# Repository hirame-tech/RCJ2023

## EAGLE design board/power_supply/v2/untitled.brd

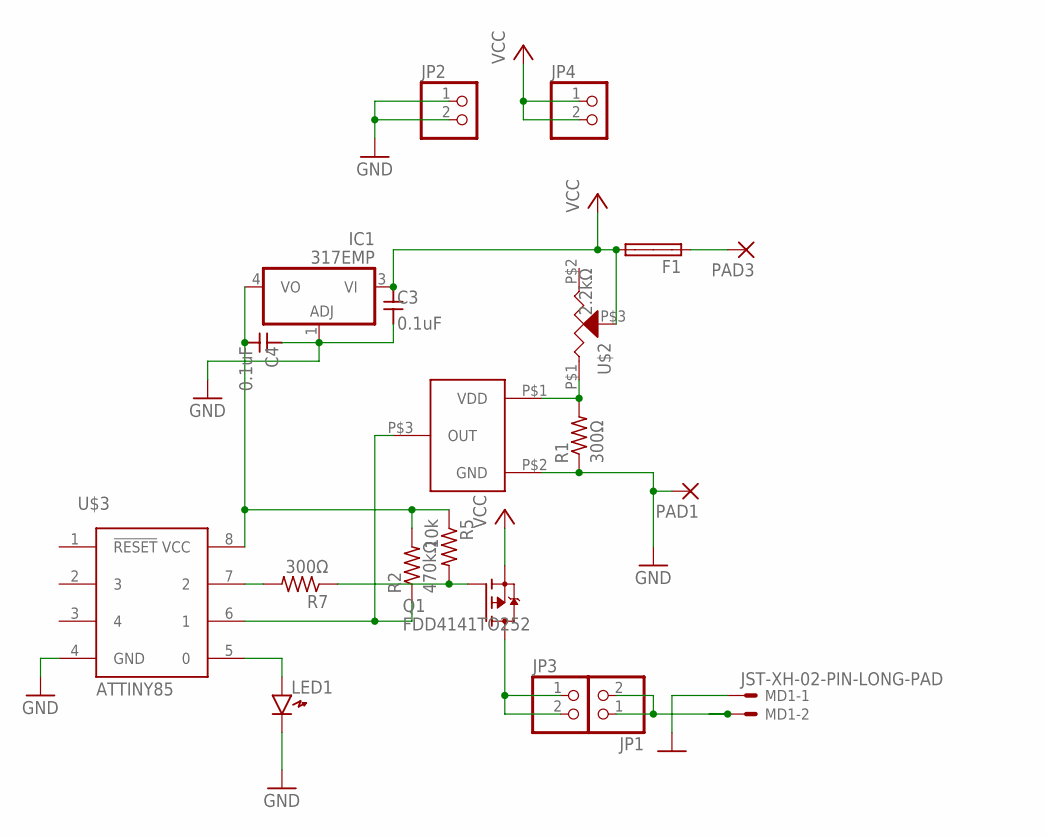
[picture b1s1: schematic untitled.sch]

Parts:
C3, C4: 0.1uF; SMD1608
F1: SH32
IC1: 317EMP; SOT223
JP1, JP2, JP3, JP4: PINHD-1X2; 1X02
LED1: LED1608
MD1: JST-XH-02-PIN-LONG-PAD; JST-XH-02-PACKAGE-LONG-PAD
PAD1, PAD3: 3,81/1,4
Q1: FDD4141TO252; TO252
R1, R7: 300Ω; M2012
R2: 470kΩ; M2012
R5: 10k; M2012
U$1: R3111N211A
U$2: 2.2kΩ; SMD-R-TRIM
U$3: ATTINY85; 8P3

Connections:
GND: C3.2, C4.1, IC1.1 (ADJ), JP2.1, JP2.2, LED1.K, MD1.1, PAD1.1, R1.1, U$1.P$2 (GND), U$3.4 (GND)
unnamed: R1.2, U$1.P$1 (VDD), U$2.P$1 (3)
unnamed: Q1.1 (G), R5.2, R7.1
unnamed: F1.1A, PAD3.1
unnamed: R2.1, U$1.P$3 (OUT), U$3.6 (1)
unnamed: JP3.1, JP3.2, Q1.3 (D)
unnamed: LED1.A, U$3.5 (0)
unnamed: JP1.1, JP1.2, MD1.2
unnamed: R7.2, U$3.7 (2)
unnamed: C4.2, IC1.4 (VO), R2.2, R5.1, U$3.8 (VCC)
VCC: C3.1, F1.2A, IC1.3 (VI), JP4.1, JP4.2, Q1.2 (S), U$2.P$3 (2)

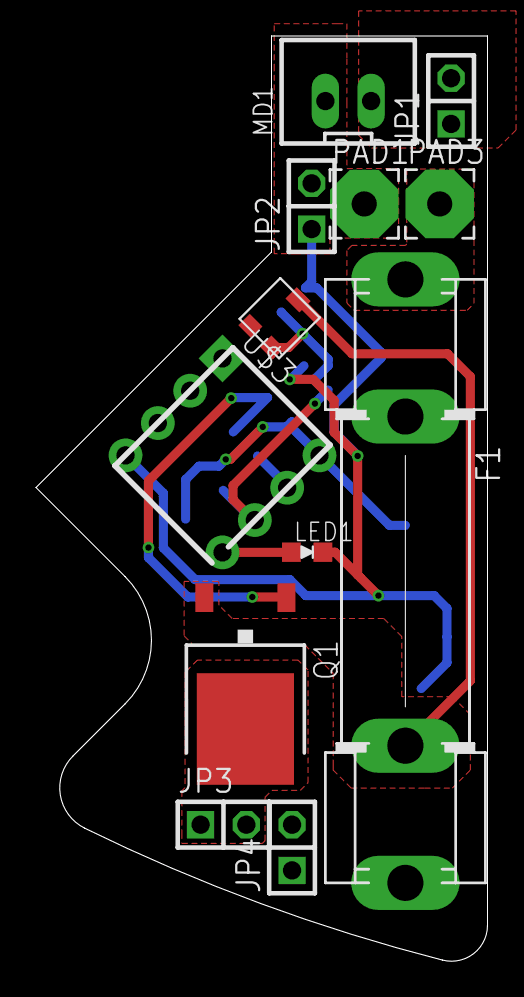
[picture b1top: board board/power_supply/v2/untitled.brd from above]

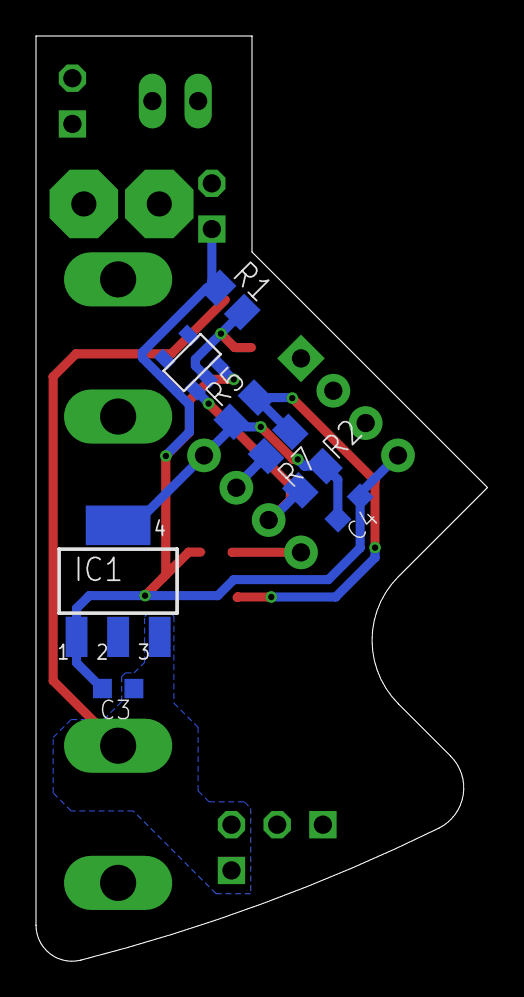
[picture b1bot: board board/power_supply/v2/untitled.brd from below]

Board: 2 copper layers, 25.1 x 51.4 mm, 20 parts (8 on the bottom side), 11 nets.

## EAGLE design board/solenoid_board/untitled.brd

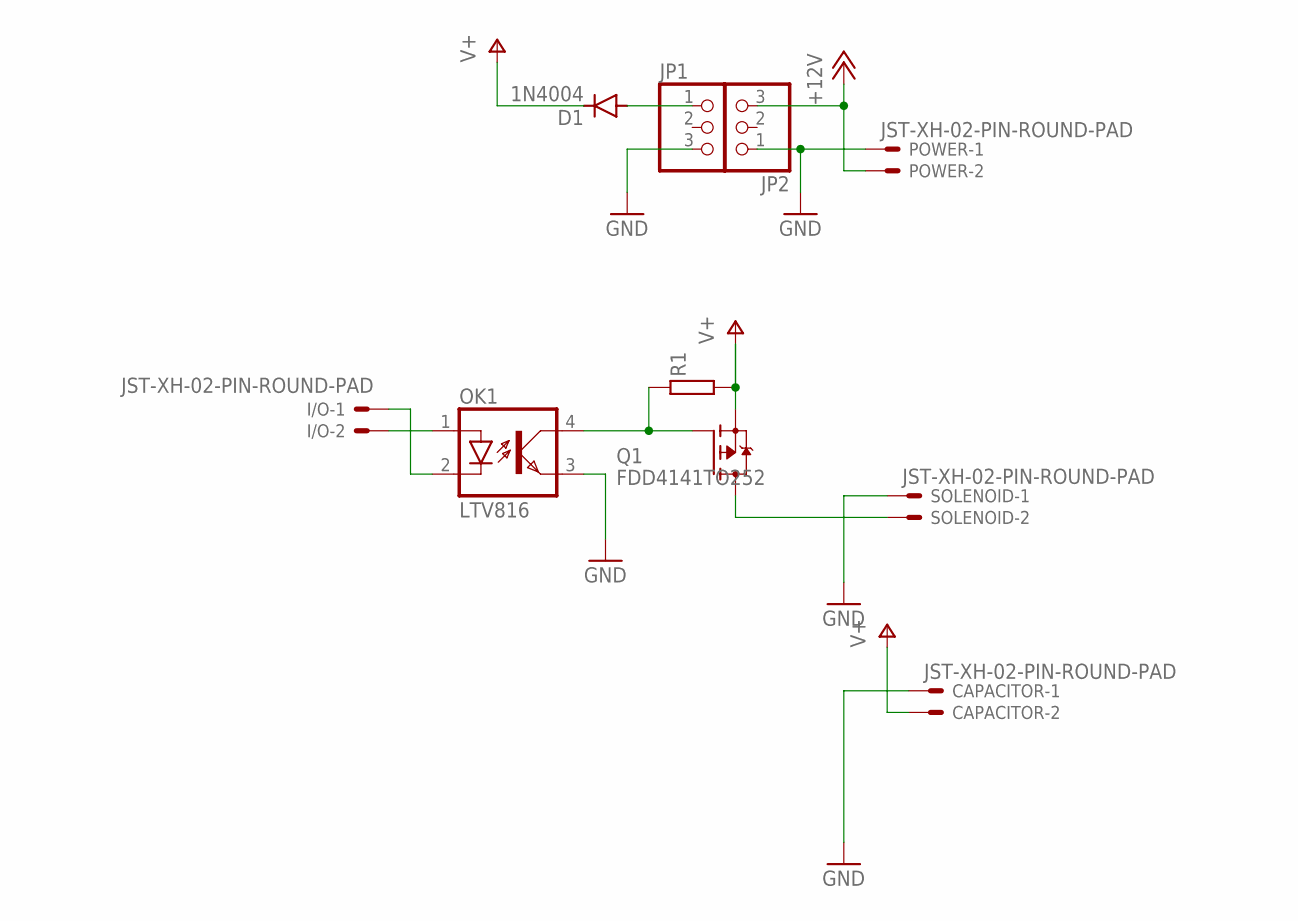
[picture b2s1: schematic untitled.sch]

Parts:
CAPACITOR: JST-XH-02-PIN-ROUND-PAD; JST-XH-02-PACKAGE-ROUND-PAD
D1: 1N4004; DO41-10
I/O: JST-XH-02-PIN-ROUND-PAD; JST-XH-02-PACKAGE-ROUND-PAD
JP1, JP2: PINHD-1X3; 1X03
OK1: LTV816; DIL04
POWER: JST-XH-02-PIN-ROUND-PAD; JST-XH-02-PACKAGE-ROUND-PAD
Q1: FDD4141TO252; TO252
R1: RESISTOR1608; SMD1608
SOLENOID: JST-XH-02-PIN-ROUND-PAD; JST-XH-02-PACKAGE-ROUND-PAD

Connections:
+12V: JP2.3, POWER.2
GND: CAPACITOR.1, JP1.3, JP2.1, OK1.3 (EMIT), POWER.1, SOLENOID.1
unnamed: Q1.3 (D), SOLENOID.2
unnamed: OK1.4 (COL), Q1.1 (G), R1.1
unnamed: I/O.2, OK1.1 (A)
unnamed: D1.A, JP1.1
unnamed: I/O.1, OK1.2 (C)
V+: CAPACITOR.2, D1.C, Q1.2 (S), R1.2

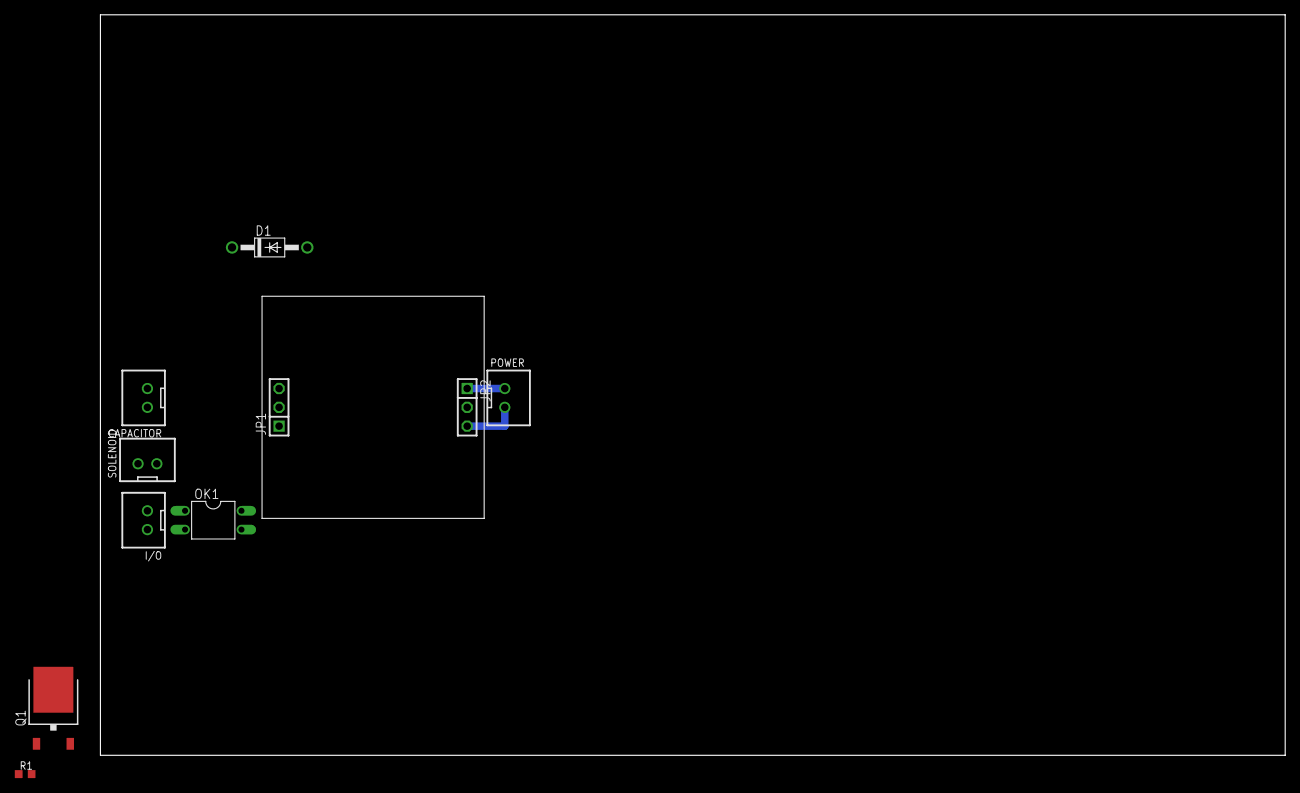
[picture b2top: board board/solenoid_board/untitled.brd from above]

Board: 2 copper layers, 160.0 x 100.0 mm, 10 parts (0 on the bottom side), 8 nets.

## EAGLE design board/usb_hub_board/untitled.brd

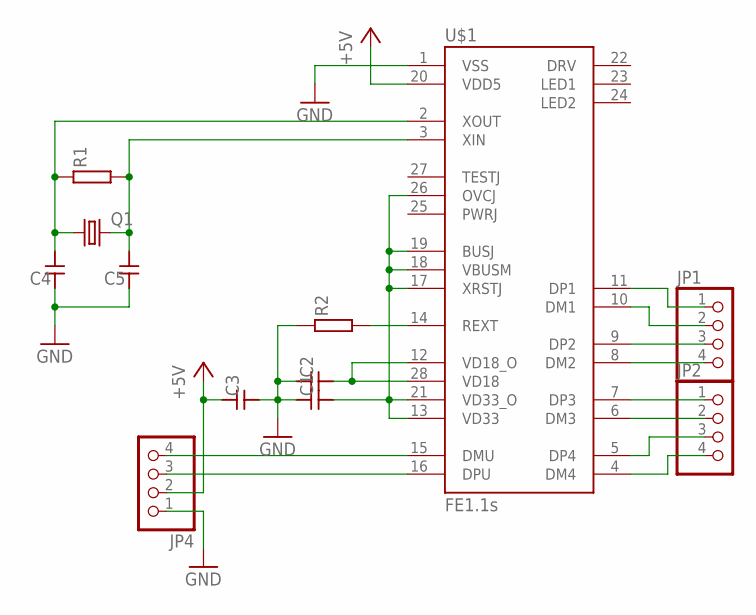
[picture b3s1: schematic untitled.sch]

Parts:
C1, C2, C3, C4, C5: CAPACITOR1608; SMD1608
JP1, JP2, JP4: PINHD-1X4; 1X04
Q1: CRYSTALHC49S; HC49/S
R1, R2: RESISTOR1608; SMD1608
U$1: FE1.1S; FE1.1S_SSOP-28

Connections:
+5V: C3.1, JP4.2, U$1.20 (VDD5)
GND: C1.1, C2.1, C3.2, C4.1, C5.1, JP4.1, R2.1, U$1.1 (VSS)
unnamed: JP4.4, U$1.15 (DMU)
unnamed: R2.2, U$1.14 (REXT)
unnamed: C2.2, U$1.12 (VD18_O), U$1.28 (VD18)
unnamed: C4.2, Q1.1, R1.1, U$1.2 (XOUT)
unnamed: C1.2, U$1.13 (VD33), U$1.17 (XRSTJ), U$1.18 (VBUSM), U$1.19 (BUSJ), U$1.21 (VD33_O), U$1.26 (OVCJ)
unnamed: C5.2, Q1.2, R1.2, U$1.3 (XIN)
unnamed: JP4.3, U$1.16 (DPU)
unnamed: JP1.4, U$1.8 (DM2)
unnamed: JP2.1, U$1.7 (DP3)
unnamed: JP2.2, U$1.6 (DM3)
unnamed: JP2.3, U$1.5 (DP4)
unnamed: JP2.4, U$1.4 (DM4)
unnamed: JP1.3, U$1.9 (DP2)
unnamed: JP1.2, U$1.10 (DM1)
unnamed: JP1.1, U$1.11 (DP1)

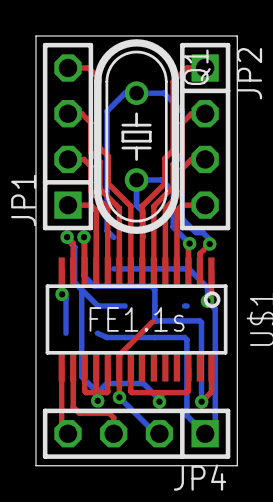
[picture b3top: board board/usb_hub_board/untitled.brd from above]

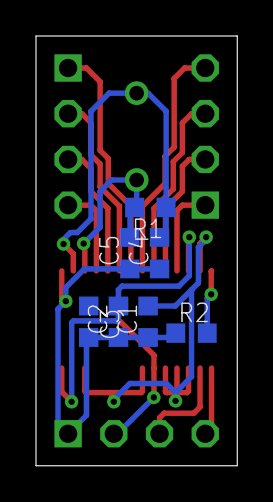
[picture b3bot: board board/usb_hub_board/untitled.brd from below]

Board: 2 copper layers, 11.2 x 23.9 mm, 12 parts (7 on the bottom side), 17 nets.
